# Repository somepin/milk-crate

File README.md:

# Milk Crate

Another milk-themed meme board, for your extra unused base kit/novelty ISO keys. Inspired by [Spaceboards/2% Milk](https://github.com/Spaceman/Spaceboards/tree/master/Keyboards/2%25%20Milk).

## Build Notes

### Printing

Print upside down slowly at ≤0.2mm layer height, with supports enabled.

### Assembly

Essentially the same as 2% Milk. I reccomend flasing the firmware to the Pro Micro before assembly.

1. Put switches into the top of the case. With the port on the left, the left switch is north facing, and the right switch is south facing. 
2. Break apart the headers to only use the required pins in the diagram below.
3. Solder short header pins to the side that says "GET SOME MILK". The plastic headers should be on the "MILK CRATE" side.
4. Insert stabilizers into the PCB. Hook side goes in to the big hole, clip/screw goes into the small hole.
5. Optionally solder RGB LED to the broken out RGB pins.
6. Insert the PCB into the case, then solder the switches.
7. Solder the Pro Micro to the header pins, making sure that the electronics are facing up.
8. Install ISO keycaps, and enjoy :)

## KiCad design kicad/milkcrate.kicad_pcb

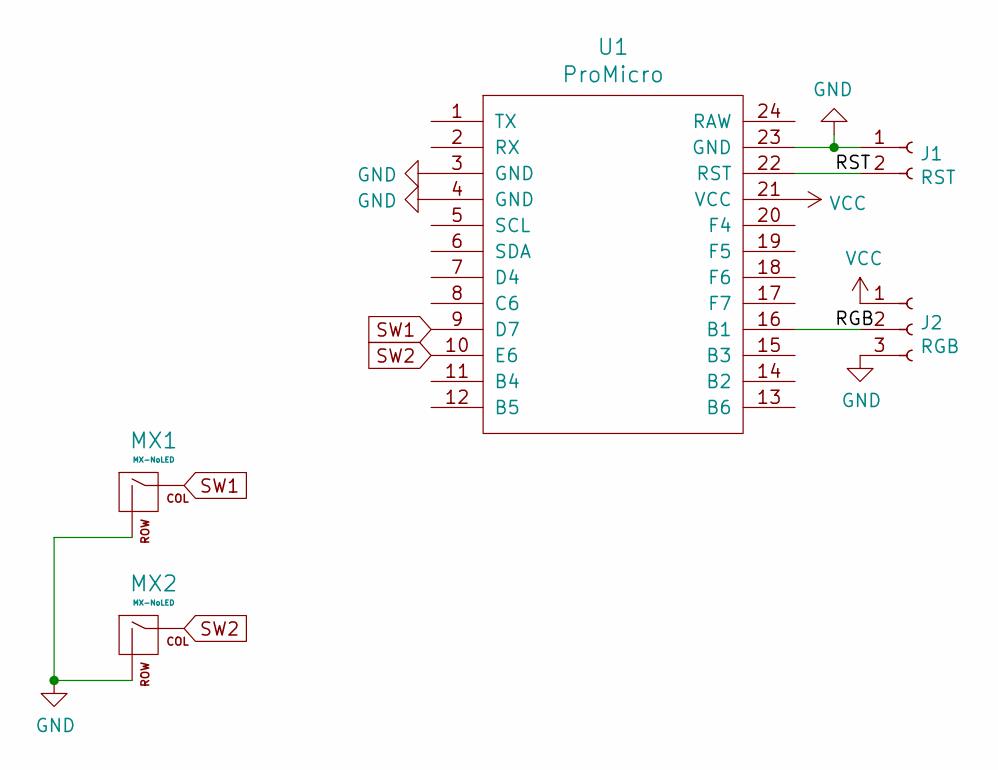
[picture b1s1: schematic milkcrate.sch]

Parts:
J1: RST; PinHeader_1x02_P2.54mm_Vertical
J2: RGB; PinHeader_1x03_P2.54mm_Vertical
MX1, MX2: MX-NoLED; MXOnly-ISO-ReversedStabilizers-NoLED
U1: ProMicro; ProMicro-NoSilk

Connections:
/RGB: J2.2, U1.16 (B1)
/RST: J1.2, U1.22 (RST)
GND: J1.1, J2.3, MX1.2 (ROW), MX2.2 (ROW), U1.3 (GND), U1.4 (GND), U1.23 (GND)
SW1: MX1.1 (COL), U1.9 (D7)
SW2: MX2.1 (COL), U1.10 (E6)
VCC: J2.1, U1.21 (VCC)

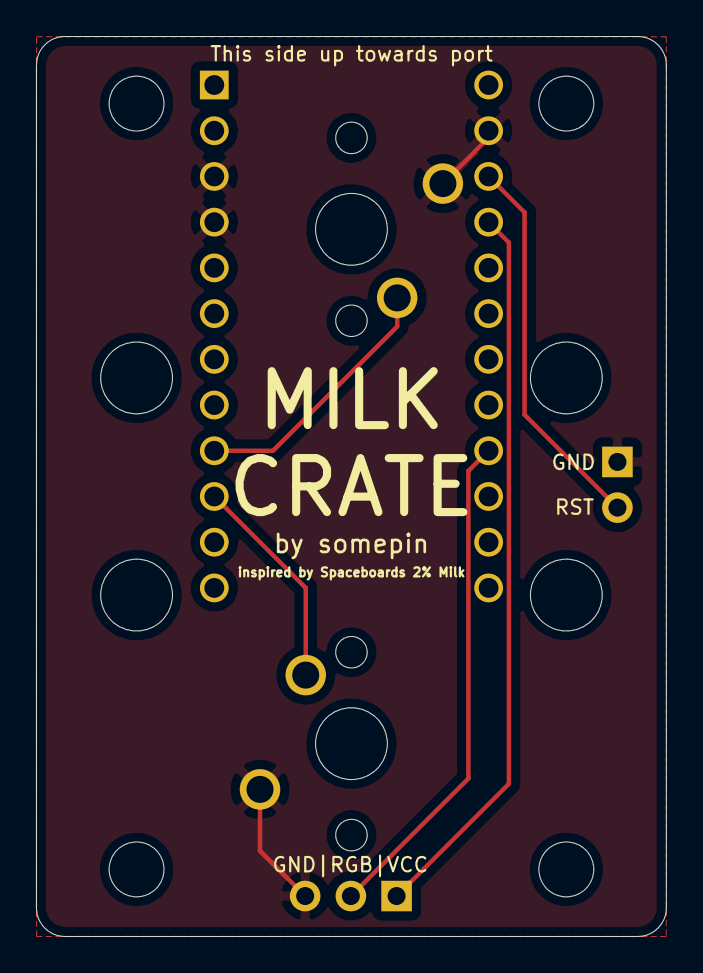
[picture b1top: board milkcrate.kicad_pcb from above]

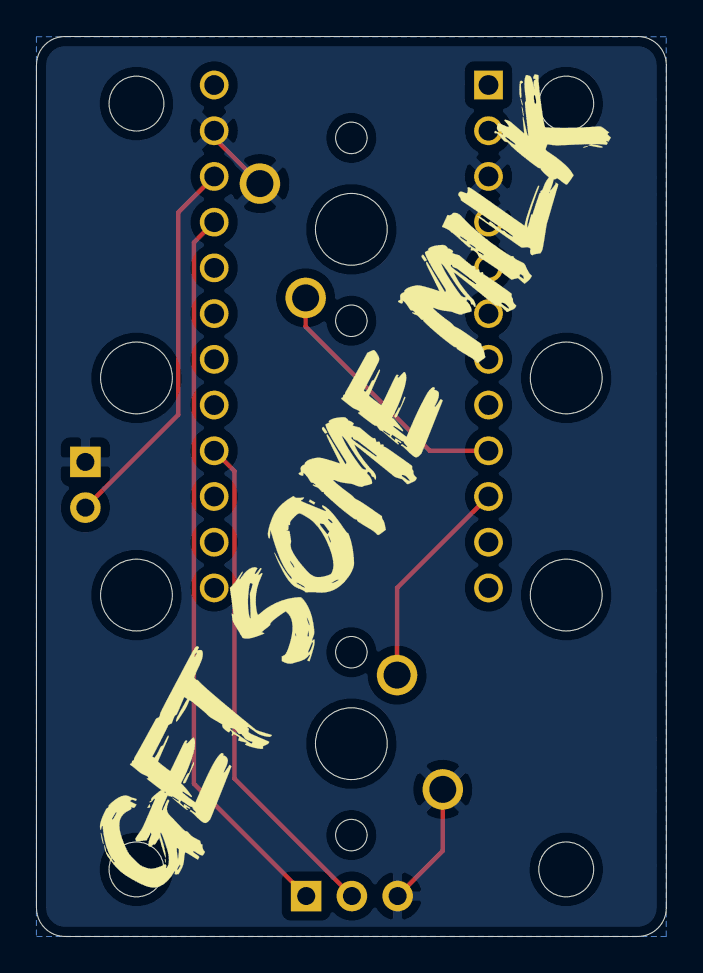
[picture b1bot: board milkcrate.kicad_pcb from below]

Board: 2 copper layers, 35.0 x 50.0 mm, 5 parts (2 on the bottom side), 6 nets.

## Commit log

2021-08-17 Create LICENSE
2021-08-17 add kicad pcb files and gerbers
2021-08-17 add case stls and step
2021-08-17 add qmk/vial firmware
